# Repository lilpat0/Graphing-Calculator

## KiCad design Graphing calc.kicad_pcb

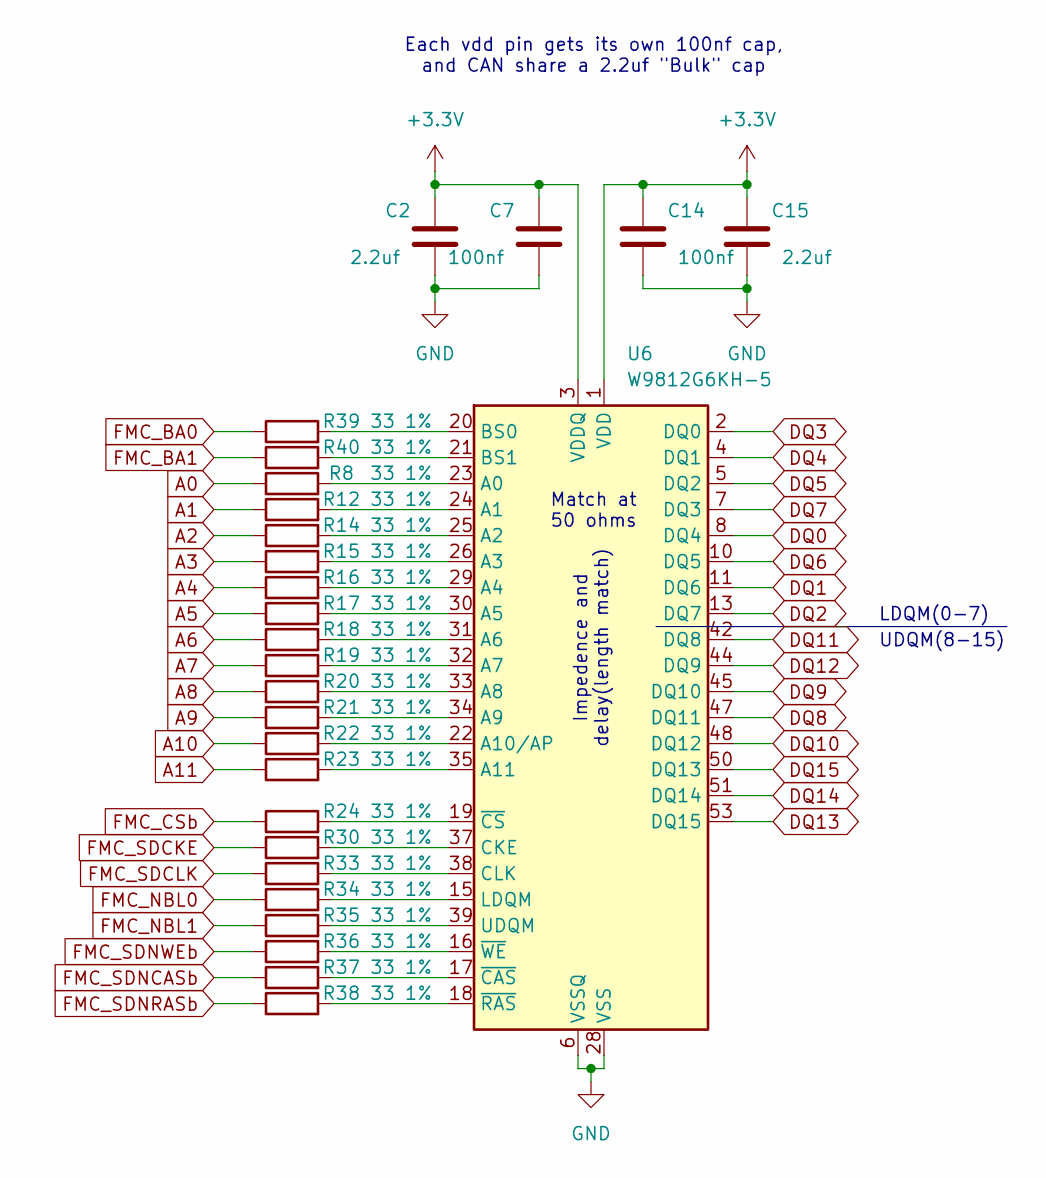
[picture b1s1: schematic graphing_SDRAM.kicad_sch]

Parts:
C2, C15: 2.2uf; C_0603_1608Metric
C7, C14: 100nf; C_0402_1005Metric
R8, R12, R14, R15, R16, R17, R18, R19, R20, R21, R22, R23, R24, R30, R33, R34, R35, R36, R37, R38, R39, R40: 33 1%; R_0201_0603Metric
U6: W9812G6KH-5; TSOP-II-54_22.2x10.16mm_P0.8mm

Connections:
+3.3V: C2.1, C7.1, C14.1, C15.1, U6.1 (VDD), U6.3 (VDDQ), U6.9 (VDDQ), U6.14 (VDD), U6.27 (VDD), U6.43 (VDDQ), U6.49 (VDDQ); also elsewhere on the board
A0: R8.1; also elsewhere on the board
A1: R12.1; also elsewhere on the board
A2: R14.1; also elsewhere on the board
A3: R15.1; also elsewhere on the board
A4: R16.1; also elsewhere on the board
A5: R17.1; also elsewhere on the board
A6: R18.1; also elsewhere on the board
A7: R19.1; also elsewhere on the board
A8: R20.1; also elsewhere on the board
A9: R21.1; also elsewhere on the board
A10: R22.1; also elsewhere on the board
A11: R23.1; also elsewhere on the board
DQ0: U6.8 (DQ4); also elsewhere on the board
DQ1: U6.11 (DQ6); also elsewhere on the board
DQ2: U6.13 (DQ7); also elsewhere on the board
DQ3: U6.2 (DQ0); also elsewhere on the board
DQ4: U6.4 (DQ1); also elsewhere on the board
DQ5: U6.5 (DQ2); also elsewhere on the board
DQ6: U6.10 (DQ5); also elsewhere on the board
DQ7: U6.7 (DQ3); also elsewhere on the board
DQ8: U6.47 (DQ11); also elsewhere on the board
DQ9: U6.45 (DQ10); also elsewhere on the board
DQ10: U6.48 (DQ12); also elsewhere on the board
DQ11: U6.42 (DQ8); also elsewhere on the board
DQ12: U6.44 (DQ9); also elsewhere on the board
DQ13: U6.53 (DQ15); also elsewhere on the board
DQ14: U6.51 (DQ14); also elsewhere on the board
DQ15: U6.50 (DQ13); also elsewhere on the board
FMC_BA0: R39.1; also elsewhere on the board
FMC_BA1: R40.1; also elsewhere on the board
FMC_CSb: R24.1; also elsewhere on the board
FMC_NBL0: R34.1; also elsewhere on the board
FMC_NBL1: R35.1; also elsewhere on the board
FMC_SDCKE: R30.1; also elsewhere on the board
FMC_SDCLK: R33.1; also elsewhere on the board
FMC_SDNCASb: R37.1; also elsewhere on the board
FMC_SDNRASb: R38.1; also elsewhere on the board
FMC_SDNWEb: R36.1; also elsewhere on the board
GND: C2.2, C7.2, C14.2, C15.2, U6.6 (VSSQ), U6.12 (VSSQ), U6.28 (VSS), U6.41 (VSS), U6.46 (VSSQ), U6.52 (VSSQ), U6.54 (VSS); also elsewhere on the board
unnamed: R8.2, U6.23 (A0)
unnamed: R12.2, U6.24 (A1)
unnamed: R14.2, U6.25 (A2)
unnamed: R15.2, U6.26 (A3)
unnamed: R16.2, U6.29 (A4)
unnamed: R17.2, U6.30 (A5)
unnamed: R18.2, U6.31 (A6)
unnamed: R19.2, U6.32 (A7)
unnamed: R20.2, U6.33 (A8)
unnamed: R21.2, U6.34 (A9)
unnamed: R22.2, U6.22 (A10/AP)
unnamed: R23.2, U6.35 (A11)
unnamed: R39.2, U6.20 (BS0)
unnamed: R40.2, U6.21 (BS1)
unnamed: R30.2, U6.37 (CKE)
unnamed: R33.2, U6.38 (CLK)
unnamed: R34.2, U6.15 (LDQM)
unnamed: R35.2, U6.39 (UDQM)
unnamed: R37.2, U6.17 (~CAS)
unnamed: R24.2, U6.19 (~CS)
unnamed: R38.2, U6.18 (~RAS)
unnamed: R36.2, U6.16 (~WE)

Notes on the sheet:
Match at 50 ohms
Each vdd pin gets its own 100nf cap, and CAN share a 2.2uf "Bulk" cap
LDQM(0-7)
Impedence and delay(length match)
UDQM(8-15)

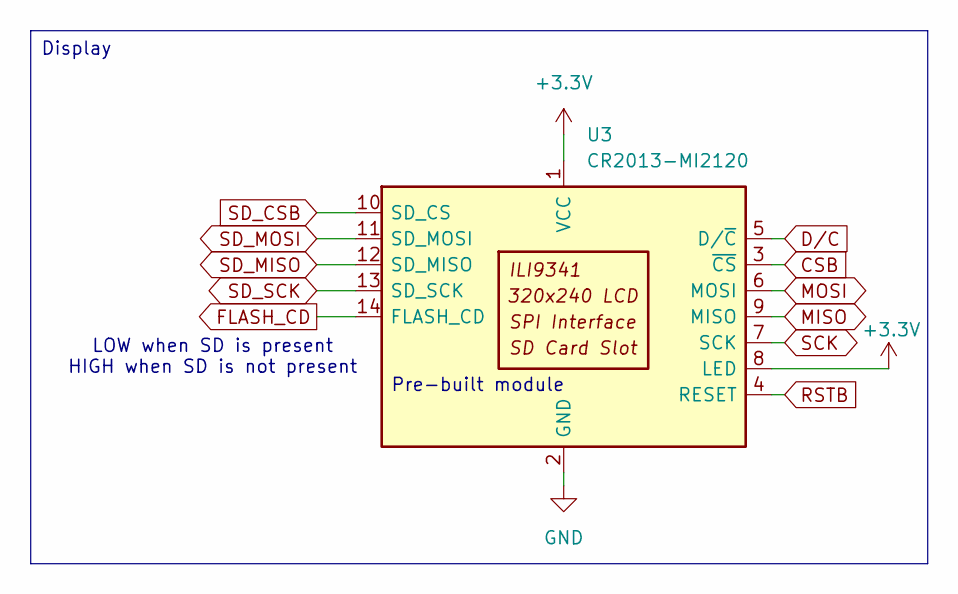
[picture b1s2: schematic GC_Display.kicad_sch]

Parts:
U3: CR2013-MI2120

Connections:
+3.3V: U3.1 (VCC), U3.8 (LED); also elsewhere on the board
CSB: U3.3 (~CS); also elsewhere on the board
D/C: U3.5 (D/~C); also elsewhere on the board
FLASH_CD: U3.14 (FLASH_CD); also elsewhere on the board
GND: U3.2 (GND); also elsewhere on the board
MISO: U3.9 (MISO); also elsewhere on the board
MOSI: U3.6 (MOSI); also elsewhere on the board
RSTB: U3.4 (RESET); also elsewhere on the board
SCK: U3.7 (SCK); also elsewhere on the board
SD_CSB: U3.10 (SD_CS); also elsewhere on the board
SD_MISO: U3.12 (SD_MISO); also elsewhere on the board
SD_MOSI: U3.11 (SD_MOSI); also elsewhere on the board
SD_SCK: U3.13 (SD_SCK); also elsewhere on the board

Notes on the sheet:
LOW when SD is present HIGH when SD is not present
Pre-built module
Display

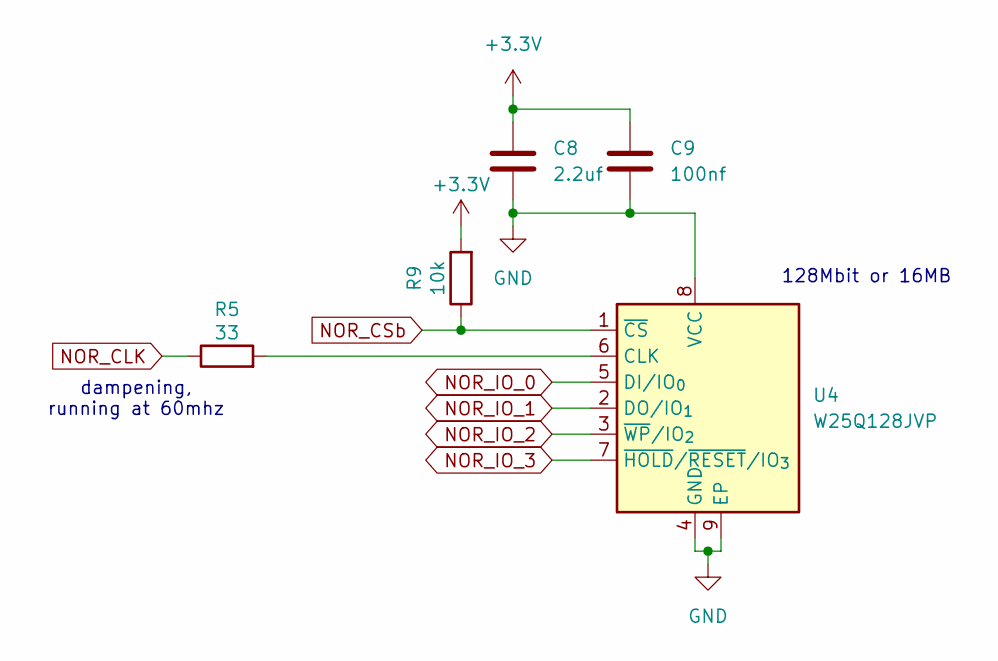
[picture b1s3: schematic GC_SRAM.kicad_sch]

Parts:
C8: 2.2uf; C_0603_1608Metric
C9: 100nf; C_0402_1005Metric
R5: 33; R_0402_1005Metric
R9: 10k; R_0402_1005Metric
U4: W25Q128JVP; WSON-8-1EP_6x5mm_P1.27mm_EP3.4x4.3mm

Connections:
+3.3V: C8.1, C9.1, R9.2; also elsewhere on the board
GND: C8.2, C9.2, U4.4 (GND), U4.8 (VCC), U4.9 (EP); also elsewhere on the board
NOR_CLK: R5.1; also elsewhere on the board
NOR_CSb: R9.1, U4.1 (~CS); also elsewhere on the board
NOR_IO_0: U4.5 (DI/IO_{0}); also elsewhere on the board
NOR_IO_1: U4.2 (DO/IO_{1}); also elsewhere on the board
NOR_IO_2: U4.3 (~WP/IO_{2}); also elsewhere on the board
NOR_IO_3: U4.7 (~HOLD/~RESET/IO_{3}); also elsewhere on the board
unnamed: R5.2, U4.6 (CLK)

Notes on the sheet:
128Mbit or 16MB
dampening, running at 60mhz

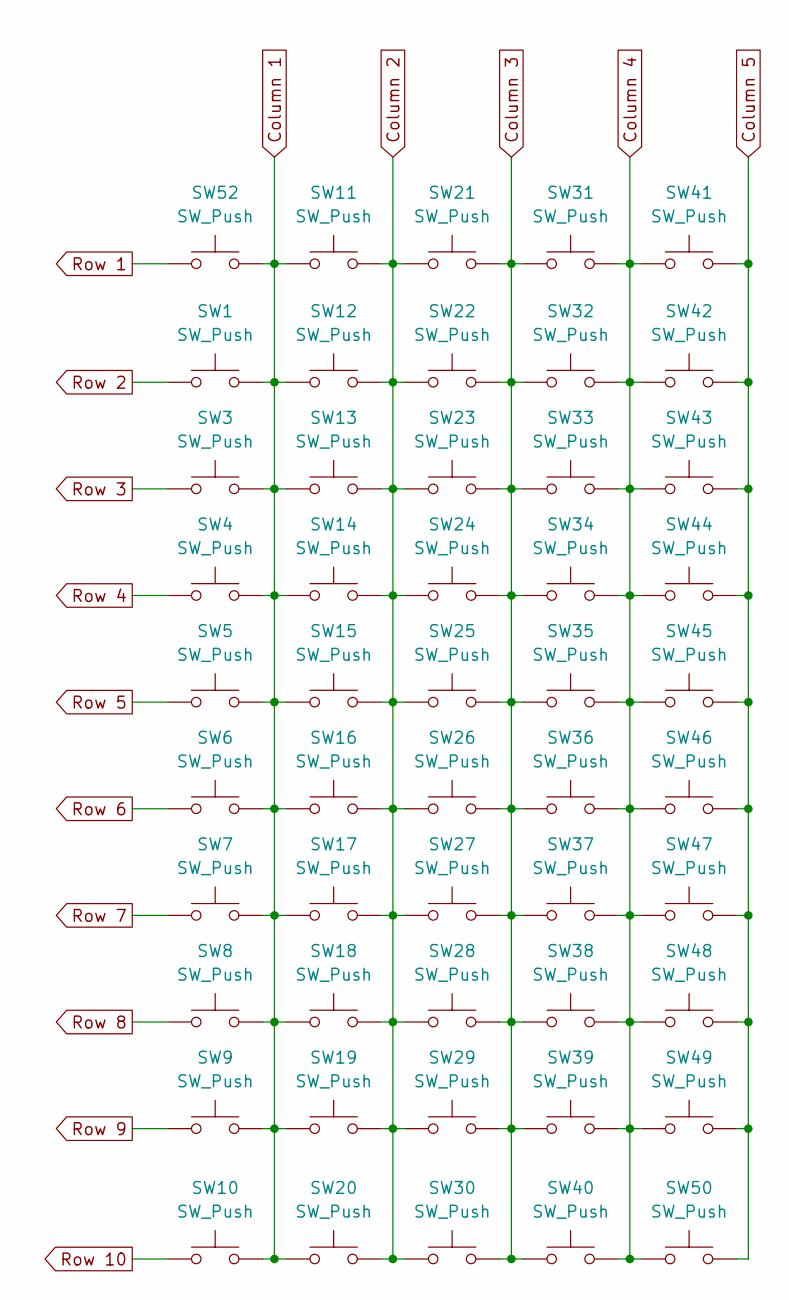
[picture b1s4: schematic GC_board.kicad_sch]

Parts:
SW1, SW3, SW4, SW5, SW6, SW7, SW8, SW9, SW10, SW11, SW12, SW13, SW14, SW15, SW16, SW17, SW18, SW19, SW20, SW21, SW22, SW23, SW24, SW25, SW26, SW27, SW28, SW29, SW30, SW31, SW32, SW33, SW34, SW35, SW36, SW37, SW38, SW39, SW40, SW41, SW42, SW43, SW44, SW45, SW46, SW47, SW48, SW49, SW50, SW52: SW_Push; SW_SPST_TL3342

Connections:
Column 1: SW1.2, SW3.2, SW4.2, SW5.2, SW6.2, SW7.2, SW8.2, SW9.2, SW10.2, SW11.1, SW12.1, SW13.1, SW14.1, SW15.1, SW16.1, SW17.1, SW18.1, SW19.1, SW20.1, SW52.2; also elsewhere on the board
Column 2: SW11.2, SW12.2, SW13.2, SW14.2, SW15.2, SW16.2, SW17.2, SW18.2, SW19.2, SW20.2, SW21.1, SW22.1, SW23.1, SW24.1, SW25.1, SW26.1, SW27.1, SW28.1, SW29.1, SW30.1; also elsewhere on the board
Column 3: SW21.2, SW22.2, SW23.2, SW24.2, SW25.2, SW26.2, SW27.2, SW28.2, SW29.2, SW30.2, SW31.1, SW32.1, SW33.1, SW34.1, SW35.1, SW36.1, SW37.1, SW38.1, SW39.1, SW40.1; also elsewhere on the board
Column 4: SW31.2, SW32.2, SW33.2, SW34.2, SW35.2, SW36.2, SW37.2, SW38.2, SW39.2, SW40.2, SW41.1, SW42.1, SW43.1, SW44.1, SW45.1, SW46.1, SW47.1, SW48.1, SW49.1, SW50.1; also elsewhere on the board
Column 5: SW41.2, SW42.2, SW43.2, SW44.2, SW45.2, SW46.2, SW47.2, SW48.2, SW49.2, SW50.2; also elsewhere on the board
Row 1: SW52.1; also elsewhere on the board
Row 2: SW1.1; also elsewhere on the board
Row 3: SW3.1; also elsewhere on the board
Row 4: SW4.1; also elsewhere on the board
Row 5: SW5.1; also elsewhere on the board
Row 6: SW6.1; also elsewhere on the board
Row 7: SW7.1; also elsewhere on the board
Row 8: SW8.1; also elsewhere on the board
Row 9: SW9.1; also elsewhere on the board
Row 10: SW10.1; also elsewhere on the board

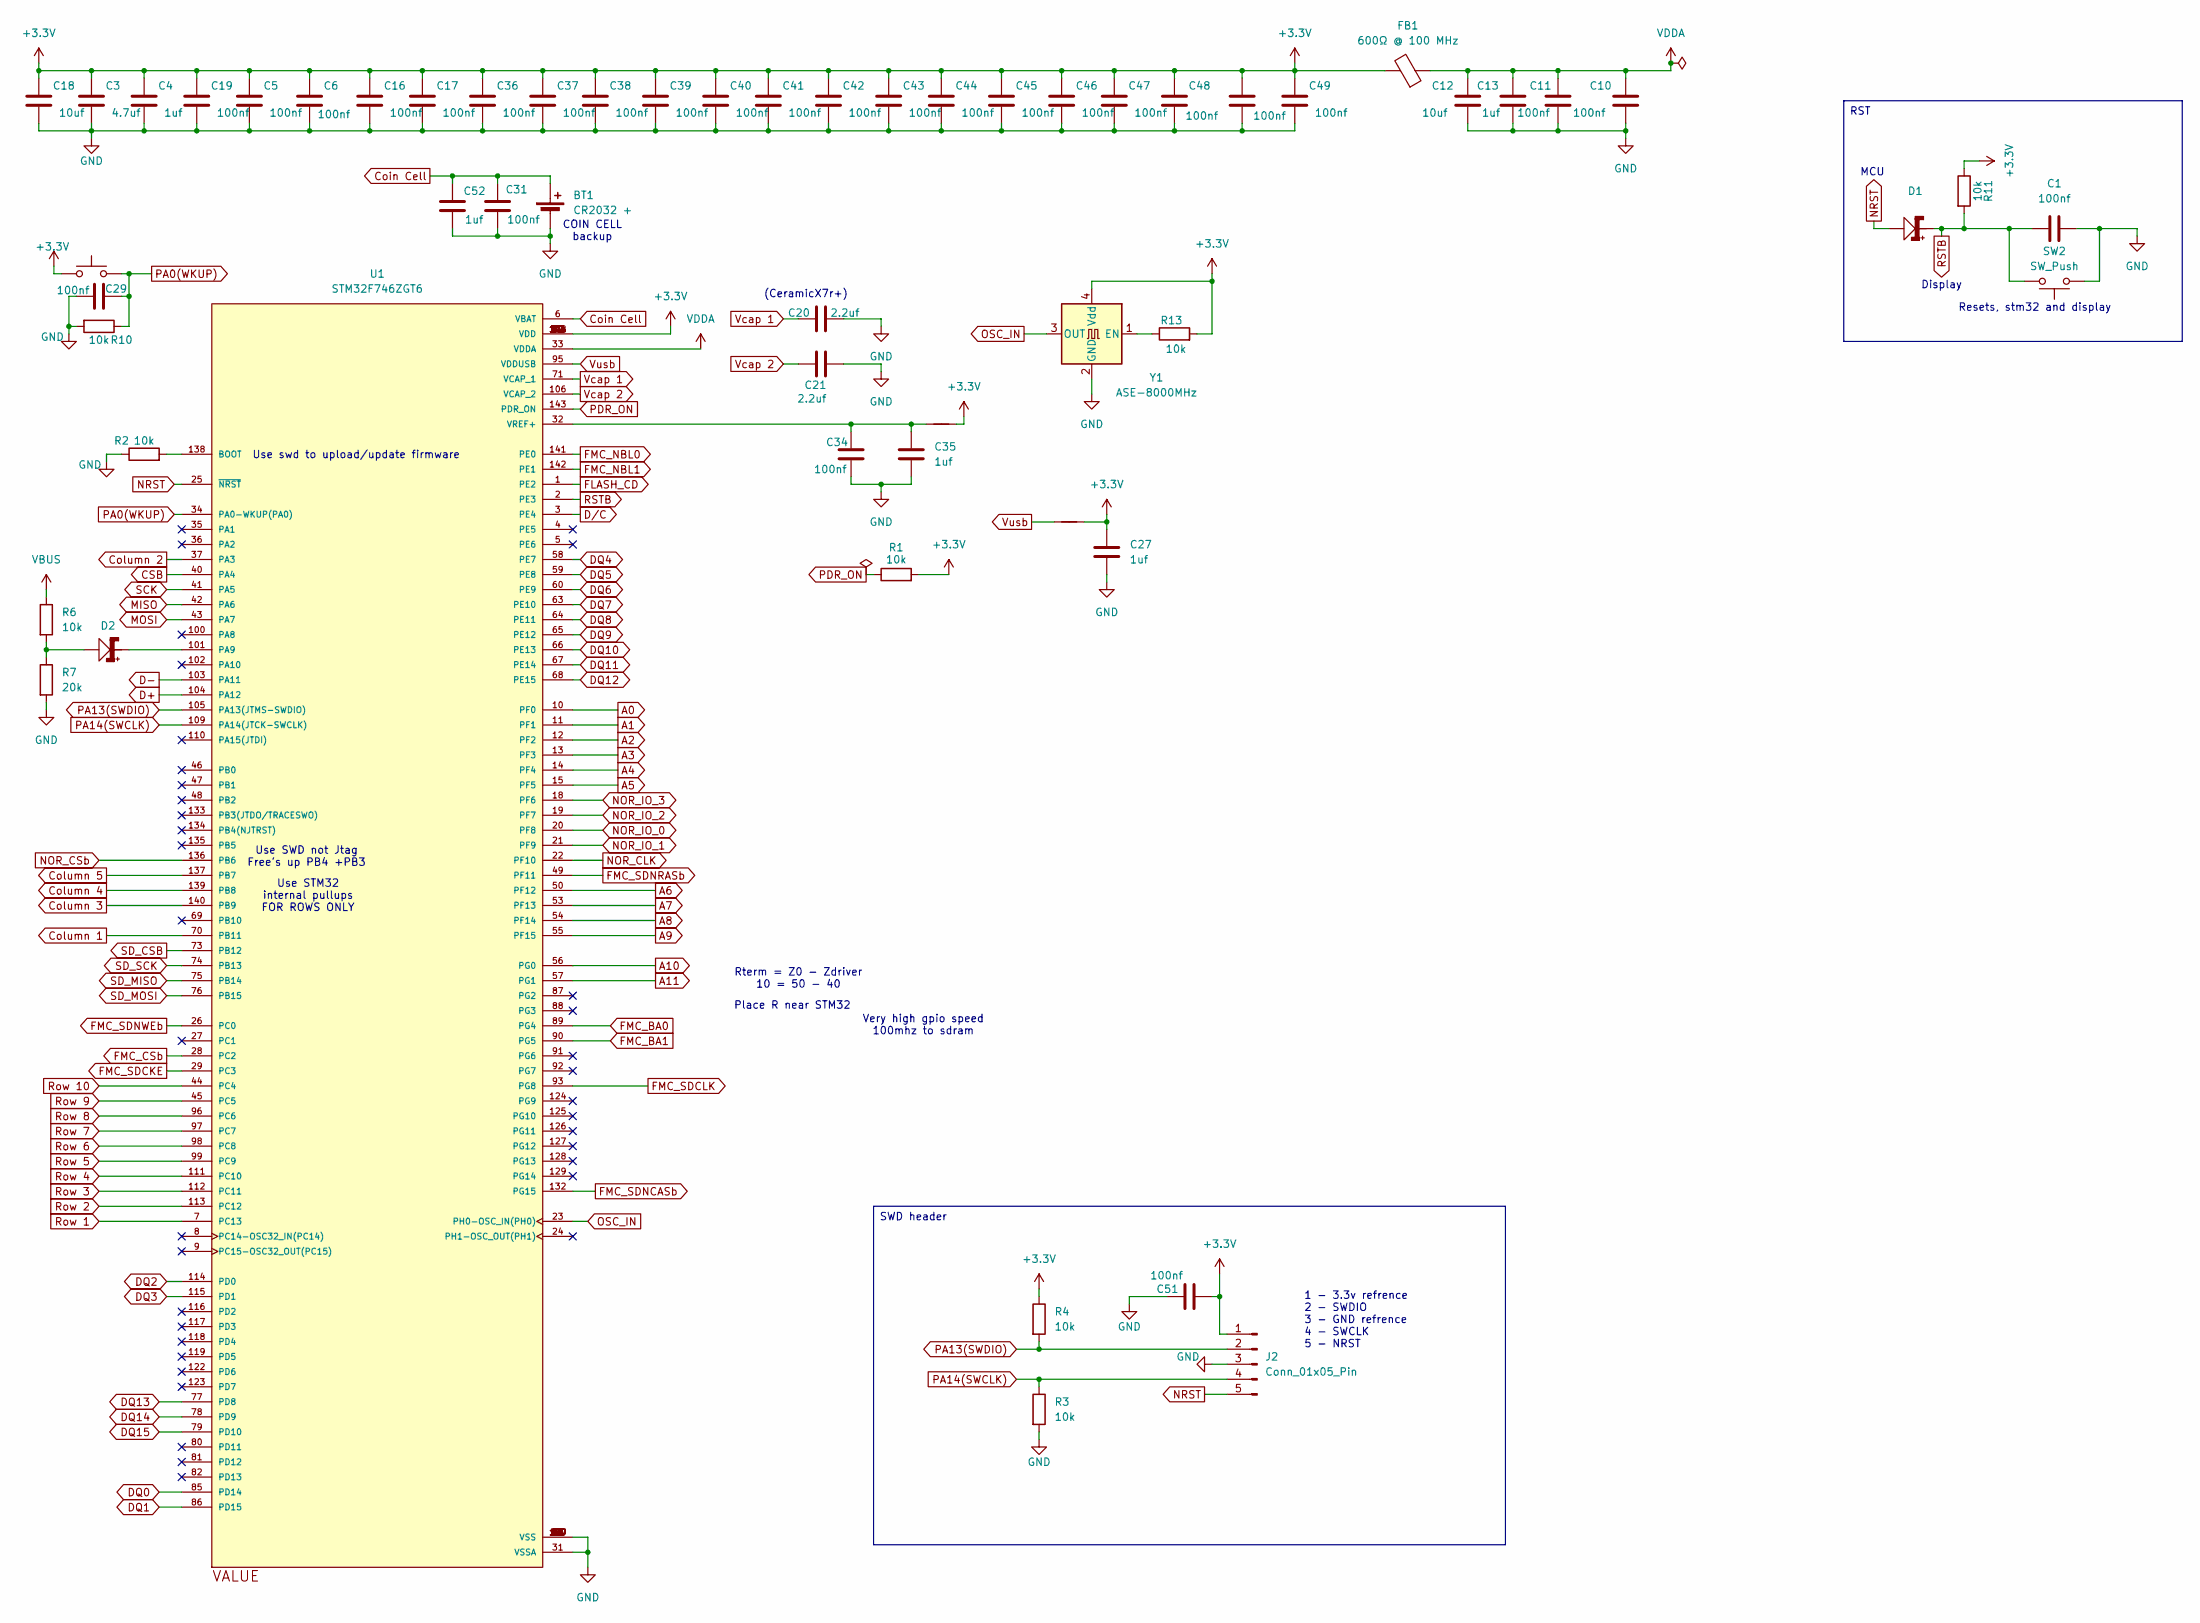
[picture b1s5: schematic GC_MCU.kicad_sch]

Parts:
BT1: CR2032 +; BatteryHolder_Keystone_1058_1x2032
C1, C5, C6, C10, C11, C16, C17, C19, C29, C31, C34, C36, C37, C38, C39, C40, C41, C42, C43, C44, C45, C46, C47, C48, C49, C50, C51: 100nf; C_0402_1005Metric
C3: 4.7uf; C_0603_1608Metric
C4, C13: 1uf; C_0603_1608Metric
C12, C18: 10uf; C_0603_1608Metric
C20, C21: 2.2uf; C_0603_1608Metric
C27, C35, C52: 1uf; C_0402_1005Metric
D1, D2: LED_0603_1608Metric
FB1: 600Ω @ 100 MHz; L_0603_1608Metric
J2: Conn_01x05_Pin; PinHeader_1x05_P2.54mm_Horizontal
NT2, NT4: NetTie_2
R1, R2, R3, R4, R6, R10, R11, R13: 10k; R_0402_1005Metric
R7: 20k; R_0402_1005Metric
SW2, SW51: SW_Push; SW_SPST_TL3342
U1: STM32F746ZGT6; PARTREV 4
Y1: ASE-8000MHz; Oscillator_SMD_Abracon_ASE-4Pin_3.2x2.5mm

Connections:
+3.3V: C3.1, C4.1, C5.1, C6.1, C16.1, C17.1, C18.1, C19.1, C27.1, C36.1, C37.1, C38.1, C39.1, C40.1, C41.1, C42.1, C43.1, C44.1, C45.1, C46.1, C47.1, C48.1, C49.1, C50.1, C51.2, FB1.2, J2.1, NT2.2, NT4.2, R1.2, R4.1, R11.1, R13.2, SW51.1, U1.17 (VDD), U1.30 (VDD), U1.39 (VDD), U1.52 (VDD), U1.62 (VDD), U1.72 (VDD), U1.84 (VDD), U1.108 (VDD), U1.121 (VDD), U1.131 (VDD), U1.144 (VDD), Y1.4 (Vdd); also elsewhere on the board
A0: U1.10 (PF0); also elsewhere on the board
A1: U1.11 (PF1); also elsewhere on the board
A2: U1.12 (PF2); also elsewhere on the board
A3: U1.13 (PF3); also elsewhere on the board
A4: U1.14 (PF4); also elsewhere on the board
A5: U1.15 (PF5); also elsewhere on the board
A6: U1.50 (PF12); also elsewhere on the board
A7: U1.53 (PF13); also elsewhere on the board
A8: U1.54 (PF14); also elsewhere on the board
A9: U1.55 (PF15); also elsewhere on the board
A10: U1.56 (PG0); also elsewhere on the board
A11: U1.57 (PG1); also elsewhere on the board
CSB: U1.40 (PA4); also elsewhere on the board
Coin Cell: BT1.1 (+), C31.1, C52.1, U1.6 (VBAT)
Column 1: U1.70 (PB11); also elsewhere on the board
Column 2: U1.37 (PA3); also elsewhere on the board
Column 3: U1.140 (PB9); also elsewhere on the board
Column 4: U1.139 (PB8); also elsewhere on the board
Column 5: U1.137 (PB7); also elsewhere on the board
D+: U1.104 (PA12); also elsewhere on the board
D-: U1.103 (PA11); also elsewhere on the board
DQ0: U1.85 (PD14); also elsewhere on the board
DQ1: U1.86 (PD15); also elsewhere on the board
DQ2: U1.114 (PD0); also elsewhere on the board
DQ3: U1.115 (PD1); also elsewhere on the board
DQ4: U1.58 (PE7); also elsewhere on the board
DQ5: U1.59 (PE8); also elsewhere on the board
DQ6: U1.60 (PE9); also elsewhere on the board
DQ7: U1.63 (PE10); also elsewhere on the board
DQ8: U1.64 (PE11); also elsewhere on the board
DQ9: U1.65 (PE12); also elsewhere on the board
DQ10: U1.66 (PE13); also elsewhere on the board
DQ11: U1.67 (PE14); also elsewhere on the board
DQ12: U1.68 (PE15); also elsewhere on the board
DQ13: U1.77 (PD8); also elsewhere on the board
DQ14: U1.78 (PD9); also elsewhere on the board
DQ15: U1.79 (PD10); also elsewhere on the board
D/C: U1.3 (PE4); also elsewhere on the board
FLASH_CD: U1.1 (PE2); also elsewhere on the board
FMC_BA0: U1.89 (PG4); also elsewhere on the board
FMC_BA1: U1.90 (PG5); also elsewhere on the board
FMC_CSb: U1.28 (PC2); also elsewhere on the board
FMC_NBL0: U1.141 (PE0); also elsewhere on the board
FMC_NBL1: U1.142 (PE1); also elsewhere on the board
FMC_SDCKE: U1.29 (PC3); also elsewhere on the board
FMC_SDCLK: U1.93 (PG8); also elsewhere on the board
FMC_SDNCASb: U1.132 (PG15); also elsewhere on the board
FMC_SDNRASb: U1.49 (PF11); also elsewhere on the board
FMC_SDNWEb: U1.26 (PC0); also elsewhere on the board
GND: BT1.2 (-), C1.2, C3.2, C4.2, C5.2, C6.2, C10.2, C11.2, C12.2, C13.2, C16.2, C17.2, C18.2, C19.2, C20.2, C21.2, C27.2, C29.1, C31.2, C34.2, C35.2, C36.2, C37.2, C38.2, C39.2, C40.2, C41.2, C42.2, C43.2, C44.2, C45.2, C46.2, C47.2, C48.2, C49.2, C50.2, C51.1, C52.2, J2.3, R2.1, R3.2, R7.2, R10.2, SW2.1, U1.16 (VSS), U1.31 (VSSA), U1.38 (VSS), U1.51 (VSS), U1.61 (VSS), U1.83 (VSS), U1.94 (VSS), U1.107 (VSS), U1.120 (VSS), U1.130 (VSS), Y1.2 (GND); also elsewhere on the board
MISO: U1.42 (PA6); also elsewhere on the board
MOSI: U1.43 (PA7); also elsewhere on the board
NOR_CLK: U1.22 (PF10); also elsewhere on the board
NOR_CSb: U1.136 (PB6); also elsewhere on the board
NOR_IO_0: U1.20 (PF8); also elsewhere on the board
NOR_IO_1: U1.21 (PF9); also elsewhere on the board
NOR_IO_2: U1.19 (PF7); also elsewhere on the board
NOR_IO_3: U1.18 (PF6); also elsewhere on the board
NRST: D1.2, J2.5, U1.25 (~NRST)
unnamed: D2.2, R6.2, R7.1
unnamed: R2.2, U1.138 (BOOT)
unnamed: D2.1, U1.101 (PA9)
unnamed: C34.1, C35.1, NT2.1, U1.32 (VREF+)
unnamed: R13.1, Y1.1 (EN)
OSC_IN: U1.23 (PH0-OSC_IN(PH0)), Y1.3 (OUT)
PA0(WKUP): C29.2, R10.1, SW51.2, U1.34 (PA0-WKUP(PA0))
PA13(SWDIO): J2.2, R4.2, U1.105 (PA13(JTMS-SWDIO))
PA14(SWCLK): J2.4, R3.1, U1.109 (PA14(JTCK-SWCLK))
PDR_ON: R1.1, U1.143 (PDR_ON)
RSTB: C1.1, D1.1, R11.2, SW2.2, U1.2 (PE3); also elsewhere on the board
Row 1: U1.7 (PC13); also elsewhere on the board
Row 2: U1.113 (PC12); also elsewhere on the board
Row 3: U1.112 (PC11); also elsewhere on the board
Row 4: U1.111 (PC10); also elsewhere on the board
Row 5: U1.99 (PC9); also elsewhere on the board
Row 6: U1.98 (PC8); also elsewhere on the board
Row 7: U1.97 (PC7); also elsewhere on the board
Row 8: U1.96 (PC6); also elsewhere on the board
Row 9: U1.45 (PC5); also elsewhere on the board
Row 10: U1.44 (PC4); also elsewhere on the board
SCK: U1.41 (PA5); also elsewhere on the board
SD_CSB: U1.73 (PB12); also elsewhere on the board
SD_MISO: U1.75 (PB14); also elsewhere on the board
SD_MOSI: U1.76 (PB15); also elsewhere on the board
SD_SCK: U1.74 (PB13); also elsewhere on the board
VBUS: R6.1; also elsewhere on the board
VDDA: C10.1, C11.1, C12.1, C13.1, FB1.1, U1.33 (VDDA)
Vcap 1: C20.1, U1.71 (VCAP_1)
Vcap 2: C21.1, U1.106 (VCAP_2)
Vusb: NT4.1, U1.95 (VDDUSB)

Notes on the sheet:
Use SWD not Jtag Free's up PB4 +PB3
Use swd to upload/update firmware
Display
Very high gpio speed 100mhz to sdram
MCU
Resets, stm32 and display
Rterm = Z0 - Zdriver 10 = 50 - 40
(CeramicX7r+)
1 - 3.3v refrence 2 - SWDIO 3 - GND refrence 4 - SWCLK 5 - NRST
Place R near STM32
COIN CELL backup
Use STM32 internal pullups FOR ROWS ONLY
RST
SWD header

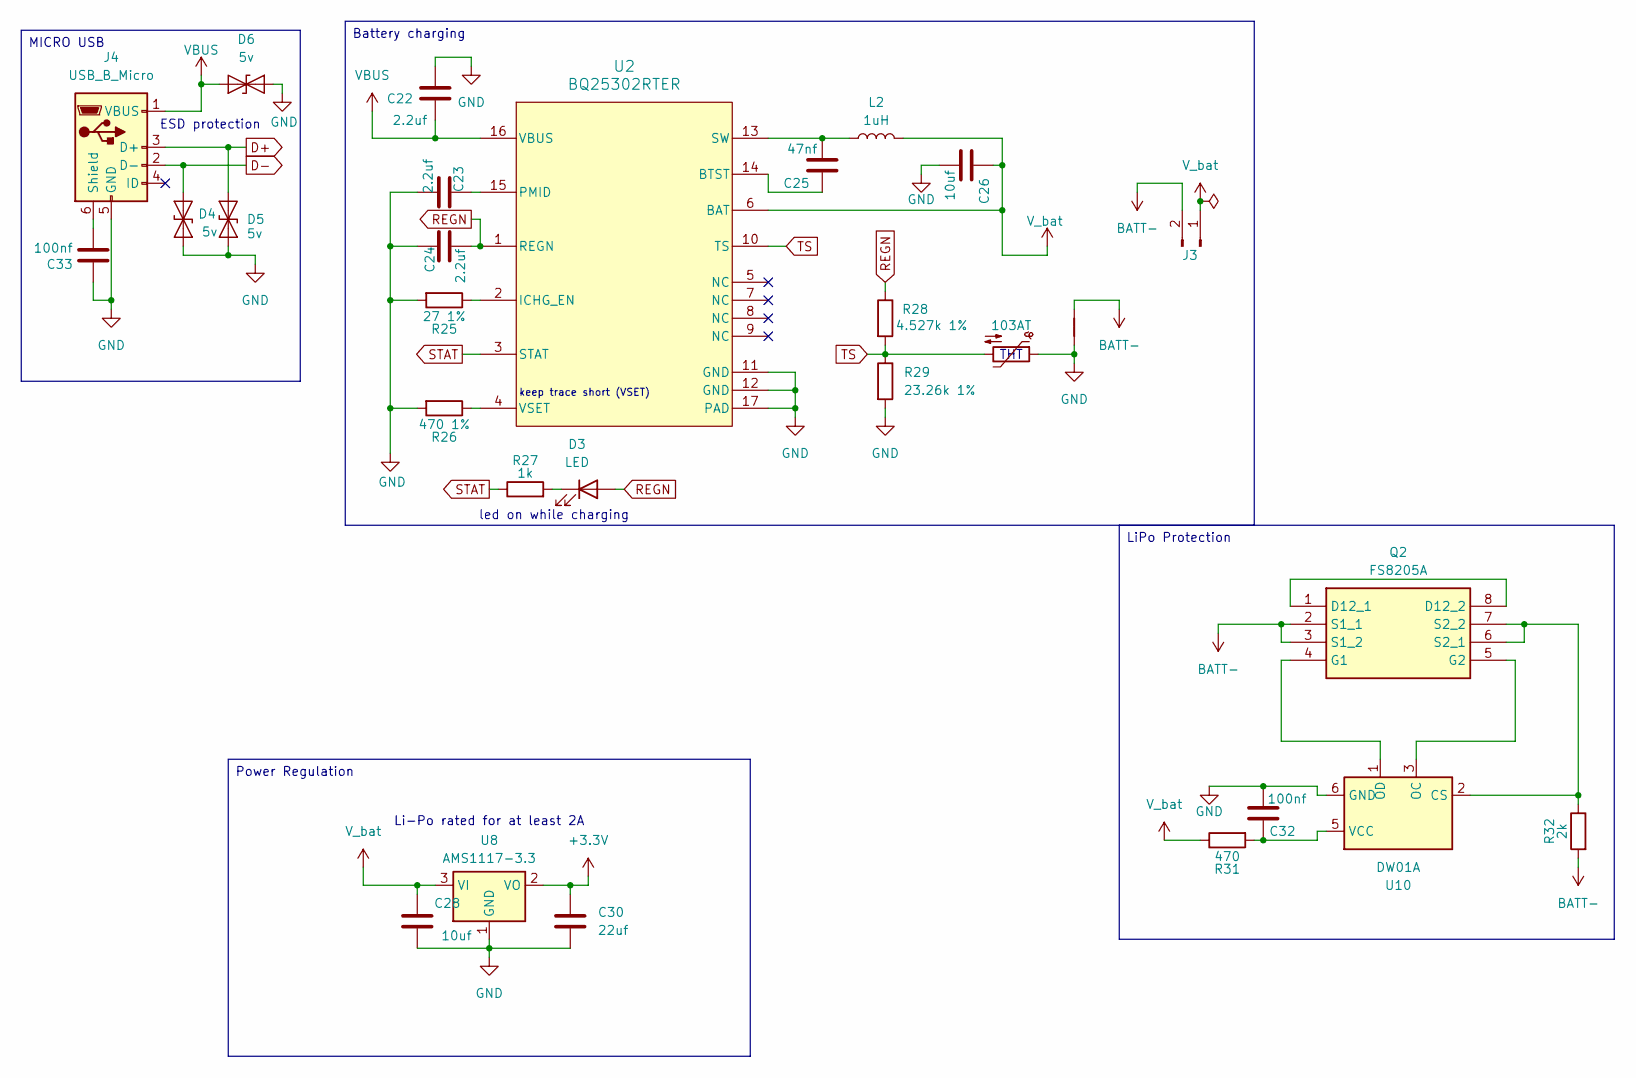
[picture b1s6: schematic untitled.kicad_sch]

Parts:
C22, C23, C24: 2.2uf; C_0402_1005Metric
C25: 47nf; C_0402_1005Metric
C26: 10uf; C_0402_1005Metric
C28: 10uf; C_0603_1608Metric
C30: 22uf; C_0603_1608Metric
C32, C33: 100nf; C_0402_1005Metric
D3: LED; LED_0603_1608Metric
D4, D5, D6: 5v; D_SOD-923
J3: Conn_01x02_Pin; PinHeader_1x02_P2.54mm_Horizontal
J4: USB_B_Micro; USB_Micro-B_Molex-105017-0001
L2: 1uH; L_0805_2012Metric
NT1: NetTie_2
Q2: FS8205A; Manufacturer_Part_Number FS8205A
R25: 27 1%; R_0402_1005Metric
R26: 470 1%; R_0402_1005Metric
R27: 1k; R_0402_1005Metric
R28: 4.527k 1%; R_0402_1005Metric
R29: 23.26k 1%; R_0402_1005Metric
R31: 470; R_0402_1005Metric
R32: 2k; R_0402_1005Metric
TH2: 103AT; R_Axial_DIN0204_L3.6mm_D1.6mm_P1.90mm_Vertical
U2: BQ25302RTER; BQ25306RTER
U8: AMS1117-3.3; SOT-223-3_TabPin2
U10: DW01A; SOT-23-6

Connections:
+3.3V: C30.1, U8.2 (VO); also elsewhere on the board
BATT-: J3.2, NT1.2, Q2.2 (S1_1), Q2.3 (S1_2), R32.2
D+: D5.2 (A2), J4.3 (D+); also elsewhere on the board
D-: D4.2 (A2), J4.2 (D-); also elsewhere on the board
GND: C22.2, C23.2, C24.1, C26.1, C28.2, C30.2, C32.2, C33.1, D4.1 (A1), D5.1 (A1), D6.1 (A1), J4.5 (GND), NT1.1, R25.2, R26.2, R29.2, TH2.1, U2.11 (GND), U2.12 (GND), U2.17 (PAD), U8.1 (GND), U10.6 (GND); also elsewhere on the board
unnamed: D3.1 (K), R27.2
unnamed: C33.2, J4.6 (Shield)
unnamed: Q2.1 (D12_1), Q2.8 (D12_2)
unnamed: Q2.4 (G1), U10.1 (OD)
unnamed: Q2.5 (G2), U10.3 (OC)
unnamed: Q2.6 (S2_1), Q2.7 (S2_2), R32.1, U10.2 (CS)
unnamed: C25.2, U2.14 (BTST)
unnamed: R25.1, U2.2 (ICHG_EN)
unnamed: C23.1, U2.15 (PMID)
unnamed: C25.1, L2.1, U2.13 (SW)
unnamed: R26.1, U2.4 (VSET)
unnamed: C32.1, R31.2, U10.5 (VCC)
REGN: C24.2, D3.2 (A), R28.1, U2.1 (REGN)
STAT: R27.1, U2.3 (STAT)
TS: R28.2, R29.1, TH2.2, U2.10 (TS)
VBUS: C22.1, D6.2 (A2), J4.1 (VBUS), U2.16 (VBUS); also elsewhere on the board
V_bat: C26.2, C28.1, J3.1, L2.2, R31.1, U2.6 (BAT), U8.3 (VI)

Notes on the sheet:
THT
led on while charging
Li-Po rated for at least 2A
keep trace short (VSET)
ESD protection
Battery charging
Power Regulation
LiPo Protection
MICRO USB

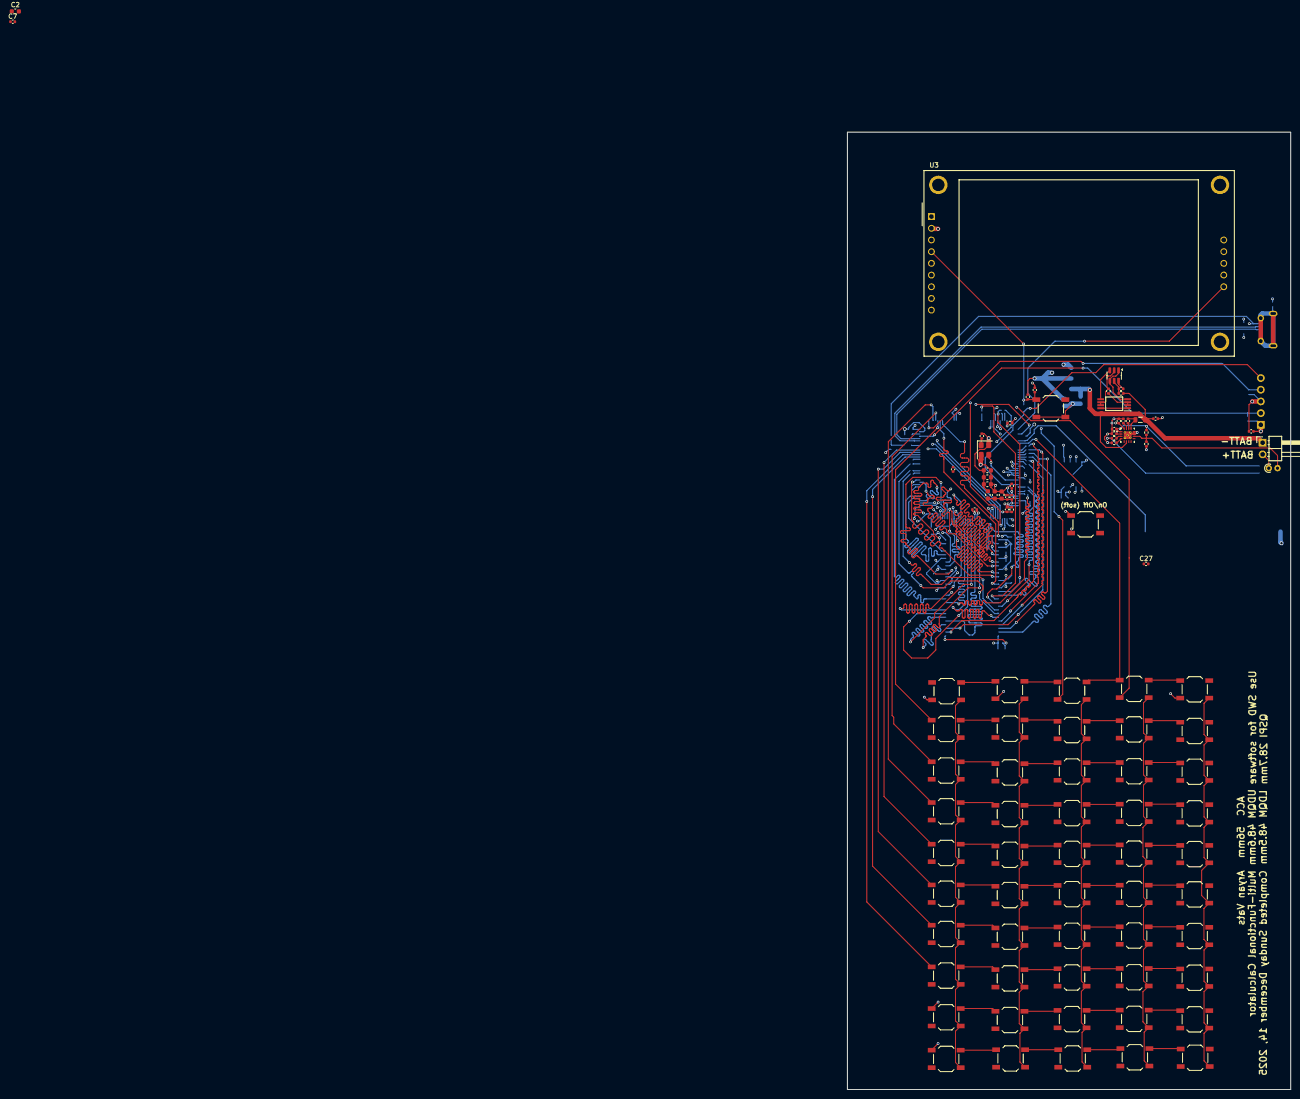
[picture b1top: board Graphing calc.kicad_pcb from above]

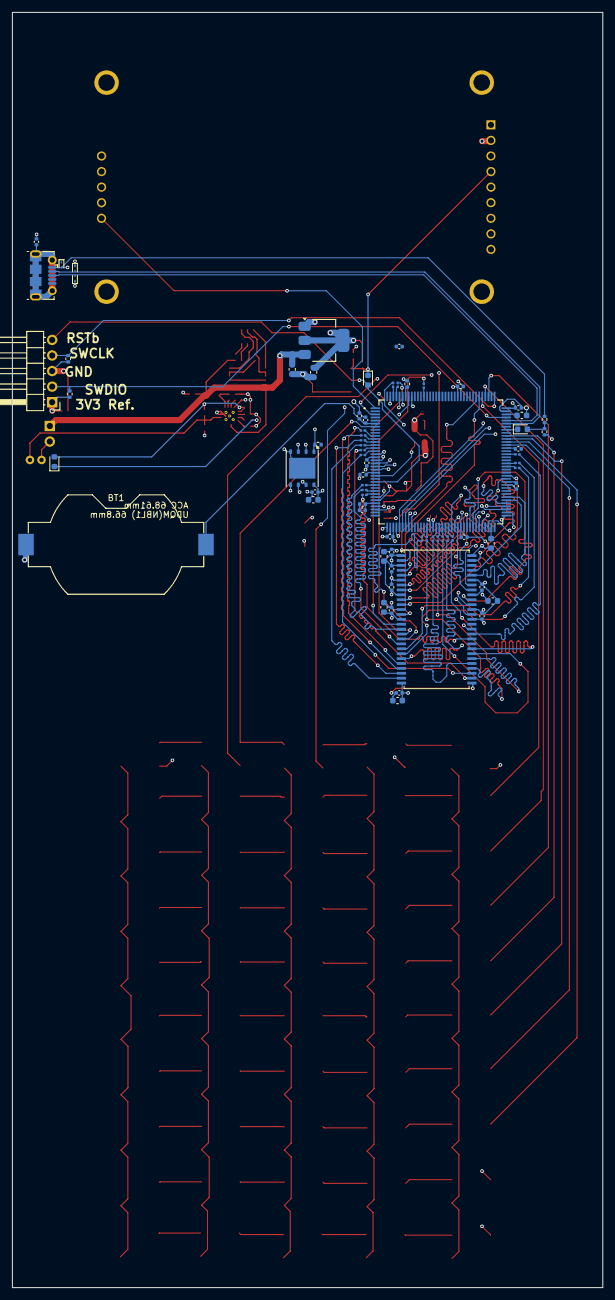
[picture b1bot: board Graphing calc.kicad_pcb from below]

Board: 6 copper layers, 96.3 x 208.0 mm, 166 parts (72 on the bottom side), 130 nets.

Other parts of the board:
C14#2, C14#3, C14#4, C14#5, C14#6, C14#7, C14#8: 100nf; C_0402_1005Metric
C15#2, C15#3, C15#4: 2.2uf; C_0603_1608Metric

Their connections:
+3.3V: C14#2.1, C14#3.1, C14#4.1, C14#5.1, C14#6.1, C14#7.1, C14#8.1, C15#2.1, C15#3.1, C15#4.1; also elsewhere on the board
GND: C14#2.2, C14#3.2, C14#4.2, C14#5.2, C14#6.2, C14#7.2, C14#8.2, C15#2.2, C15#3.2, C15#4.2; also elsewhere on the board
